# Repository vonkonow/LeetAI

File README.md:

# 🎹 Leet AI – A Tiny Synth Ensemble with AI-Powered Inspiration

Leet AI is a playful, pocket-sized synthesizer concept that explores what happens when many simple instruments work together—like a miniature electronic orchestra. Unlike traditional synths that try to do everything, Leet AI embraces a modular philosophy: multiple open-source, affordable units, each with a specific voice, combining to create something greater than the sum of their parts.

---

## 🌟 Why Leet AI?

Synthesizers can be intimidating. Menus, shift-buttons, and buried features can kill creative flow. Leet AI is an attempt to bring back the fun—tiny instruments you can pick up, jam with, and let the AI surprise you with new melodic ideas. Whether you're a tinkerer, a musician, or just curious about AI and music, this project is for you.

---

## ✨ Features

- 🎵 **AI-powered inspiration**  
  Generate unique melodies, drum patterns, and variations using a diffusion-based AI model.

- 🔧 **Hackable and open-source**  
  Built with CircuitPython on an ESP32-S2—plug it in, and you're editing the firmware like a USB stick.

- 🎛️ **Minimalist design with deep control**  
  Dual rotary encoders with tilt navigation, RGB-backlit keys, and a full-color display keep you focused and in control.

- 📶 **Wireless orchestration**  
  A low-latency protocol keeps multiple units in sync.

- 🔋 **Fully portable**  
  Runs on a rechargeable 1000mAh LiPo battery. Jam anywhere.

---

## 📦 Hardware Specs

- **Size:** 86 x 60 x 15 mm (smaller than a deck of cards!)
- **Keys:** 16 RGB-backlit mechanical keys
- **Microcontroller:** ESP32-S2 (CircuitPython firmware)
- **Display:** 1.8” 160x128 TFT color screen
- **Encoders:** Dual magnetic rotary encoders with tilt function
- **Audio:** High-quality 112dB SNR DAC
- **Connectivity:** MIDI over USB-C, ESP-Now wireless sync
- **Power:** 1000mAh LiPo battery with onboard charging

---

# ▶️ **Demo video** 

---

## 🧪 Build Difficulty 

**Medium.** You'll need SMD soldering skills, a 3D printer, and some patience and curiosity.

---

## 🛠️ Development History

Leet AI combines the best aspects of three earlier open hardware projects: [**leet**](https://vonkonow.com/leet-synthesizer/), [**leet modular**](https://vonkonow.com/leet-modular/), and [**chip champ**](https://vonkonow.com/chipchamp/). Prototypes have evolved through countless iterations—from hand-wired mock-ups to a 12-key prototype and finally to the 16-key design that bridges sequencer and keyboard layouts.

---

## 🚧 Limitations (For Now)

This is still a conceptual prototype. While it’s fully functional for the demo, many features are hardcoded. Here’s what’s next on the roadmap:

- 🎚️ Real-time editing and melody creation  
- 🎵 Higher-fidelity audio engine and custom graphic module
- 🎛️ Instrument selection and sound design (ADSR, filters, etc.)  
- 🧠 Smarter AI integration with automatic Wi-Fi server connection  
- 🎹 Stacked octave mode  
- 🔊 Optional speaker  
- 🎶 AMY synth library support?

---

## 🛒 BOM / Estimated Cost

**Total cost per unit:** ~$24

---

## 💡 Contributing

Got ideas? Want to help improve the synth engine, optimize graphics, or design new enclosures? All contributions—code, hardware, or creative—are welcome!

### ➕ How to Contribute

1. Fork the repo  
2. Try the demo firmware  
3. Submit issues or pull requests  
4. Join the discussion on hardware, AI models, or interface design

---

## 📁 Repository Structure

```
/
├── firmware/       → CircuitPython source code
├── hardware/       → KiCad files, schematics, and PCB layout
├── enclosure/      → 3D models (Rhino & STL)
├── ai-server/      → getMusic setup, scripts and generation tools
├── docs/           → Build guide, BOM, and reference images
└── README.md       → Project overview
```

---

## ❤️ Special Thanks

Huge thanks to the creators and maintainers of open-source tools that made this project possible.  
Special gratitude to [**Adafruit**](https://www.adafruit.com/) for developing [**CircuitPython**](https://circuitpython.org/board/lolin_s2_mini/), which made firmware development approachable, flexible, and fun—even for hardware newcomers.  
Thanks also to the team behind [**synthio**](https://docs.circuitpython.org/en/latest/shared-bindings/synthio/), whose powerful audio capabilities laid the groundwork for expressive, real-time sound generation on microcontrollers.  
And to Microsoft Research for [**getMusic**](https://github.com/microsoft/muzic), and to all the explorers at the intersection of music, AI, and creative technology—your curiosity and generosity continue to inspire.

---

## 🧠 Imagine What’s Next

Leet AI is still early, but the concept is alive. With your feedback, forks, and experiments, this can grow into a truly modular, generative instrument playground.

---

## 🔗 [Visit the project website  ](https://vonkonow.com/leetai/)
## 📂 [Explore the GitHub repository  ](https://github.com/vonkonow/leetai)
## 📸 [Share your builds and music!](https://vonkonow.com/community/)

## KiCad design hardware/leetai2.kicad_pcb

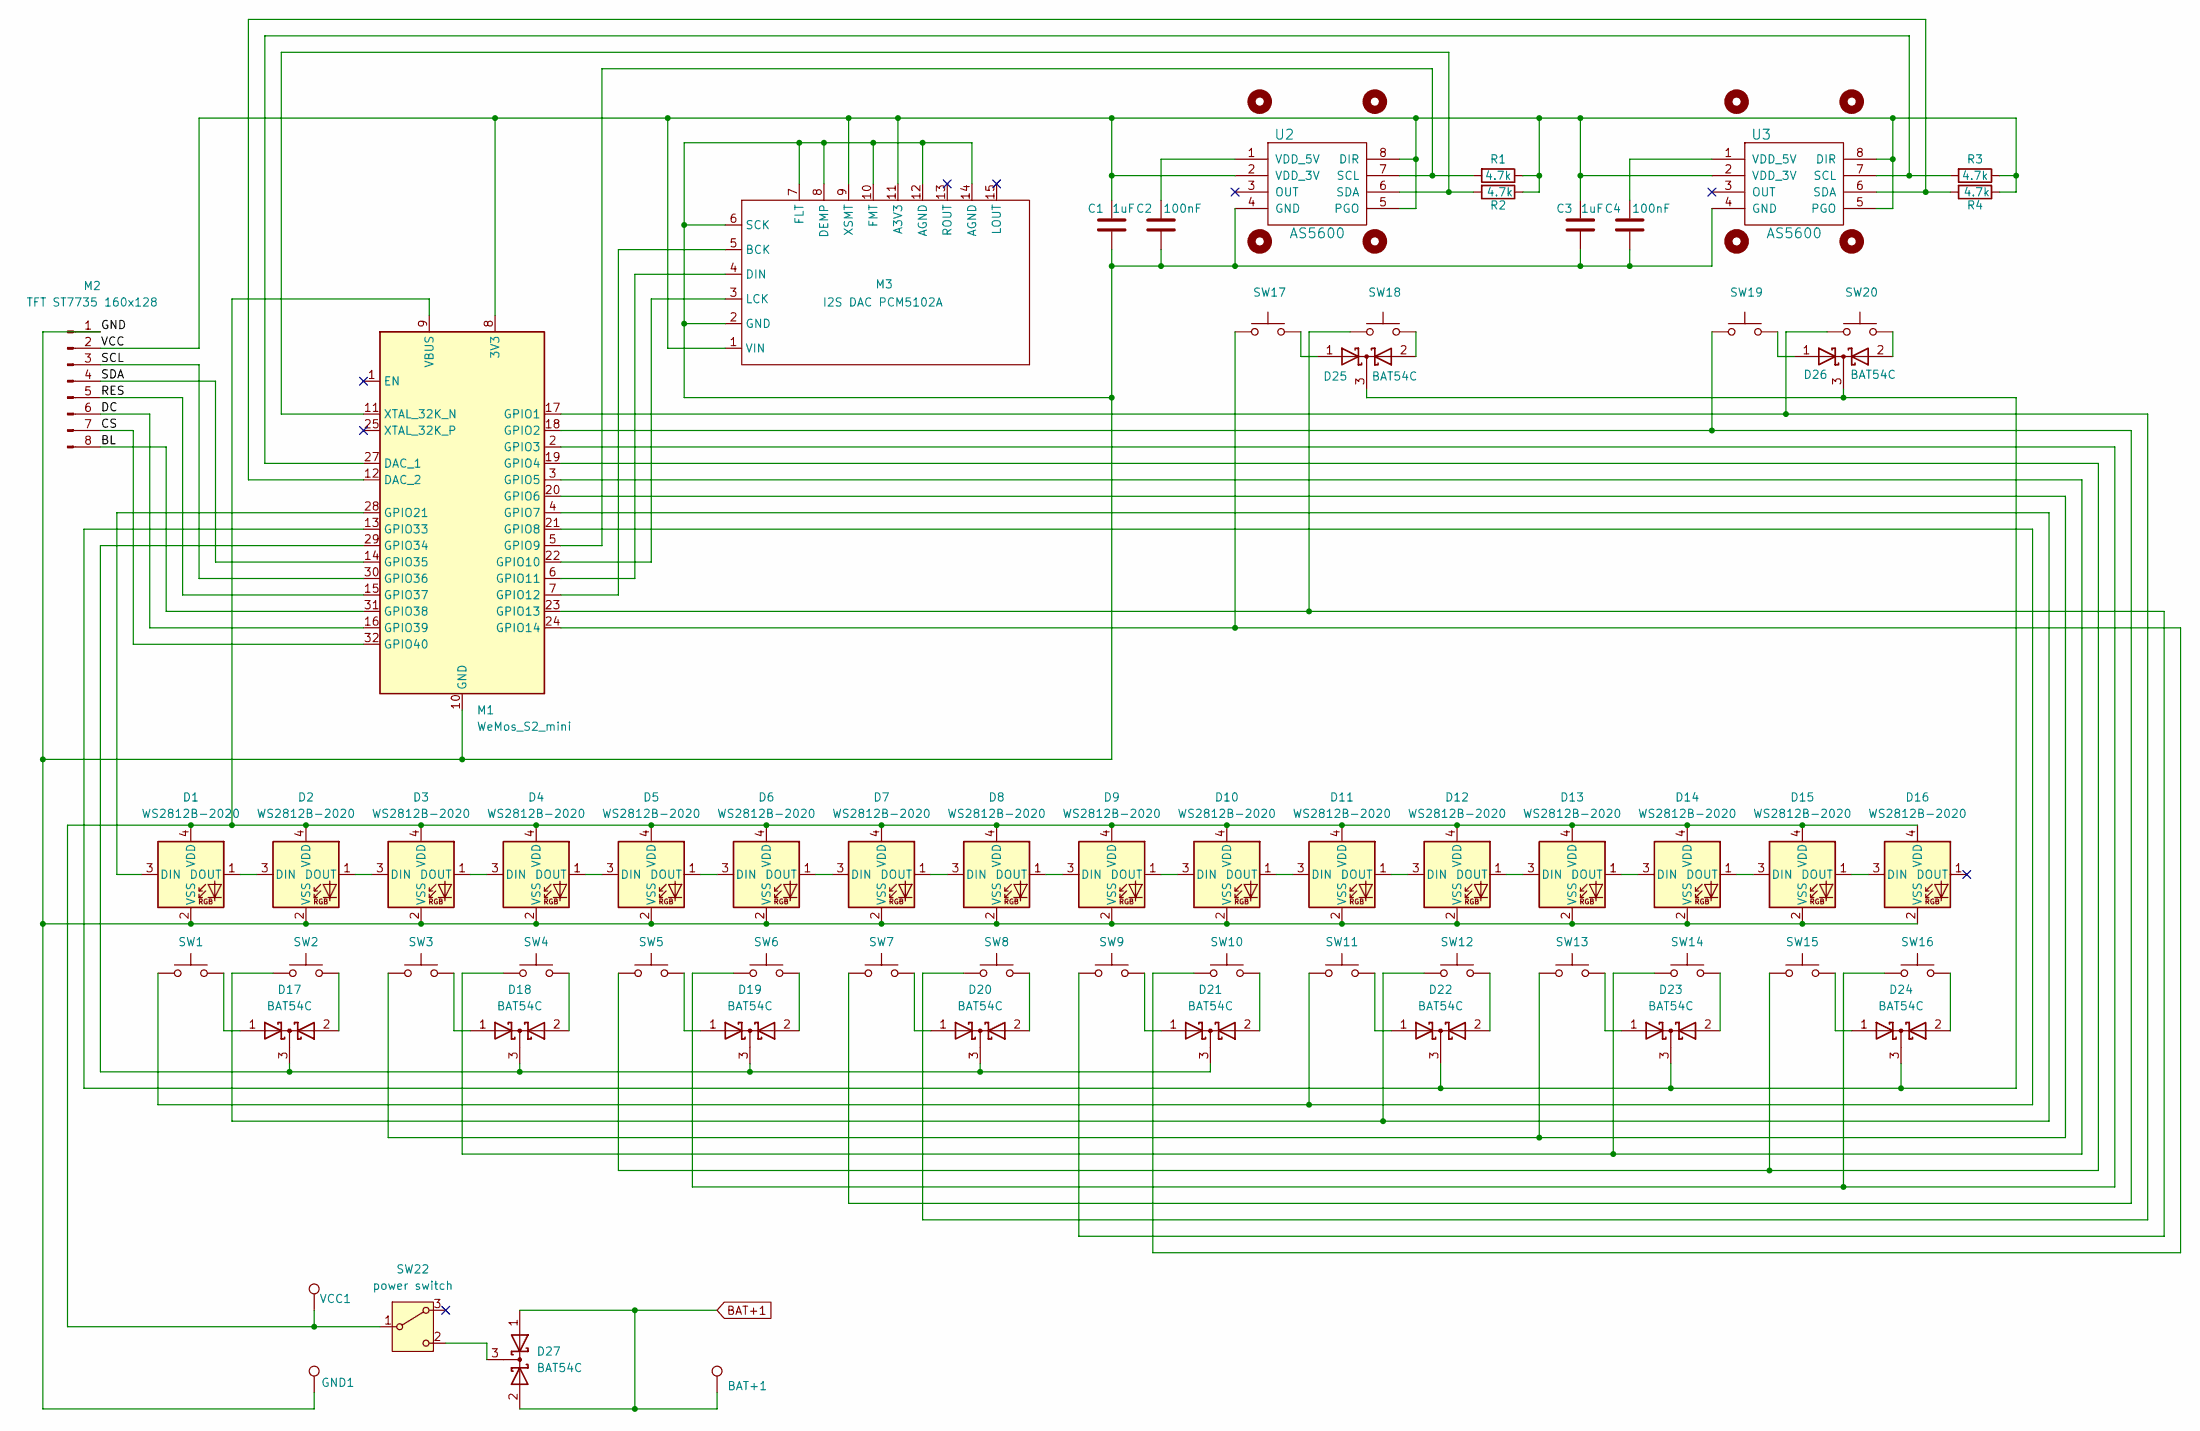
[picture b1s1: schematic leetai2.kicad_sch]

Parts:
BAT+1: Conn_01x01_Female; TestPoint_THTPad_2.5x2.5mm_Drill1.2mm
C1, C3: 1uF; C_0603_1608Metric_Pad1.08x0.95mm_HandSolder
C2, C4: 100nF; C_0603_1608Metric_Pad1.08x0.95mm_HandSolder
D1, D2, D3, D4, D5, D6, D7, D8, D9, D10, D11, D12, D13, D14, D15, D16: WS2812B-2020; LED_WS2812B-2020_PLCC4_2.0x2.0mm
D17, D18, D19, D20, D21, D22, D23, D24, D25, D26, D27: BAT54C; TSOT-23
GND1: Conn_01x01_Female; TestPoint_THTPad_2.5x2.5mm_Drill1.2mm
H1, H2, H3, H4, H5, H6, H7, H8: MountingHole; MountingHole_2mm
M1: WeMos_S2_mini; wemos_s2_mini
M2: TFT ST7735 160x128
M3: I2S DAC PCM5102A; I2S DAC 5102
R1, R2, R3, R4: 4.7k; R_0603_1608Metric_Pad0.98x0.95mm_HandSolder
SW1, SW2, SW3, SW4, SW5, SW6, SW7, SW8, SW9, SW10, SW11, SW12, SW13, SW14, SW15, SW16: SW_Omron_B3FS; switch_mouse_kailh_6x6
SW17, SW18, SW19, SW20: SW_Omron_B3FS; SW_Push_SPST_NO_Alps_SKRK
SW22: power switch; SW_Slide-03_Wuerth-WS-SLTV_10x2.5x6.4_P2.54mm
U2, U3: AS5600; SOIC-8_3.9x4.9mm_P1.27mm; Manufacturer Part Number AS5600-ASOM
VCC1: Conn_01x01_Female; TestPoint_THTPad_2.5x2.5mm_Drill1.2mm

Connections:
/BL: M1.31 (GPIO38), M2.8
/CS: M1.32 (GPIO40), M2.7
/DC: M1.16 (GPIO39), M2.6
/GND: C1.2, C2.1, C3.2, C4.1, D1.2 (VSS), D2.2 (VSS), D3.2 (VSS), D4.2 (VSS), D5.2 (VSS), D6.2 (VSS), D7.2 (VSS), D8.2 (VSS), D9.2 (VSS), D10.2 (VSS), D11.2 (VSS), D12.2 (VSS), D13.2 (VSS), D14.2 (VSS), D15.2 (VSS), D16.2 (VSS), GND1.1, M1.10 (GND), M1.26 (GND), M2.1, M3.2 (GND), M3.6 (SCK), M3.7 (FLT), M3.8 (DEMP), M3.10 (FMT), M3.12 (AGND), M3.14 (AGND), U2.4 (GND), U3.4 (GND)
/RES: M1.15 (GPIO37), M2.5
/SCL: M1.30 (GPIO36), M2.3
/SDA: M1.14 (GPIO35), M2.4
/VCC: C1.1, C3.1, M1.8 (3V3), M2.2, M3.1 (VIN), M3.9 (XSMT), M3.11 (A3V3), R1.1, R2.1, R3.1, R4.1, U2.2 (VDD_3V), U2.5 (PGO), U2.8 (DIR), U3.2 (VDD_3V), U3.5 (PGO), U3.8 (DIR)
BAT+1: BAT+1.1, D27.1 (A), D27.2 (A); also elsewhere on the board
unnamed: D1.3 (DIN), M1.28 (GPIO21)
unnamed: D1.1 (DOUT), D2.3 (DIN)
unnamed: D1.4 (VDD), D2.4 (VDD), D3.4 (VDD), D4.4 (VDD), D5.4 (VDD), D6.4 (VDD), D7.4 (VDD), D8.4 (VDD), D9.4 (VDD), D10.4 (VDD), D11.4 (VDD), D12.4 (VDD), D13.4 (VDD), D14.4 (VDD), D15.4 (VDD), D16.4 (VDD), M1.9 (VBUS), SW22.1 (B), VCC1.1
unnamed: D2.1 (DOUT), D3.3 (DIN)
unnamed: D3.1 (DOUT), D4.3 (DIN)
unnamed: D4.1 (DOUT), D5.3 (DIN)
unnamed: D5.1 (DOUT), D6.3 (DIN)
unnamed: D6.1 (DOUT), D7.3 (DIN)
unnamed: D7.1 (DOUT), D8.3 (DIN)
unnamed: D8.1 (DOUT), D9.3 (DIN)
unnamed: D9.1 (DOUT), D10.3 (DIN)
unnamed: D10.1 (DOUT), D11.3 (DIN)
unnamed: D11.1 (DOUT), D12.3 (DIN)
unnamed: D12.1 (DOUT), D13.3 (DIN)
unnamed: D13.1 (DOUT), D14.3 (DIN)
unnamed: D14.1 (DOUT), D15.3 (DIN)
unnamed: D15.1 (DOUT), D16.3 (DIN)
unnamed: D17.1 (A), SW1.2
unnamed: D17.2 (A), SW2.2
unnamed: D17.3 (K), D18.3 (K), D19.3 (K), D20.3 (K), D21.3 (K), M1.29 (GPIO34)
unnamed: D18.1 (A), SW3.2
unnamed: D18.2 (A), SW4.2
unnamed: D19.1 (A), SW5.2
unnamed: D19.2 (A), SW6.2
unnamed: D20.1 (A), SW7.2
unnamed: D20.2 (A), SW8.2
unnamed: D21.1 (A), SW9.2
unnamed: D21.2 (A), SW10.2
unnamed: D22.1 (A), SW11.2
unnamed: D22.2 (A), SW12.2
unnamed: D22.3 (K), D23.3 (K), D24.3 (K), D25.3 (K), D26.3 (K), M1.13 (GPIO33)
unnamed: D23.1 (A), SW13.2
unnamed: D23.2 (A), SW14.2
unnamed: D24.1 (A), SW15.2
unnamed: D24.2 (A), SW16.2
unnamed: D25.1 (A), SW17.2
unnamed: D25.2 (A), SW18.2
unnamed: D26.1 (A), SW19.2
unnamed: D26.2 (A), SW20.2
unnamed: D27.3 (K), SW22.2 (C)
unnamed: M1.27 (DAC_1), R3.2, U3.7 (SCL)
unnamed: M1.12 (DAC_2), R4.2, U3.6 (SDA)
unnamed: M1.17 (GPIO1), SW8.1, SW20.1
unnamed: M1.18 (GPIO2), SW7.1, SW19.1
unnamed: M1.2 (GPIO3), SW6.1, SW16.1
unnamed: M1.19 (GPIO4), SW5.1, SW15.1
unnamed: M1.3 (GPIO5), SW4.1, SW14.1
unnamed: M1.20 (GPIO6), SW3.1, SW13.1
unnamed: M1.4 (GPIO7), SW2.1, SW12.1
unnamed: M1.21 (GPIO8), SW1.1, SW11.1
unnamed: M1.5 (GPIO9), R1.2, U2.7 (SCL)
unnamed: M1.22 (GPIO10), M3.3 (LCK)
unnamed: M1.6 (GPIO11), M3.4 (DIN)
unnamed: M1.7 (GPIO12), M3.5 (BCK)
unnamed: M1.23 (GPIO13), SW9.1, SW18.1
unnamed: M1.24 (GPIO14), SW10.1, SW17.1
unnamed: M1.11 (XTAL_32K_N), R2.2, U2.6 (SDA)
unnamed: C2.2, U2.1 (VDD_5V)
unnamed: C4.2, U3.1 (VDD_5V)

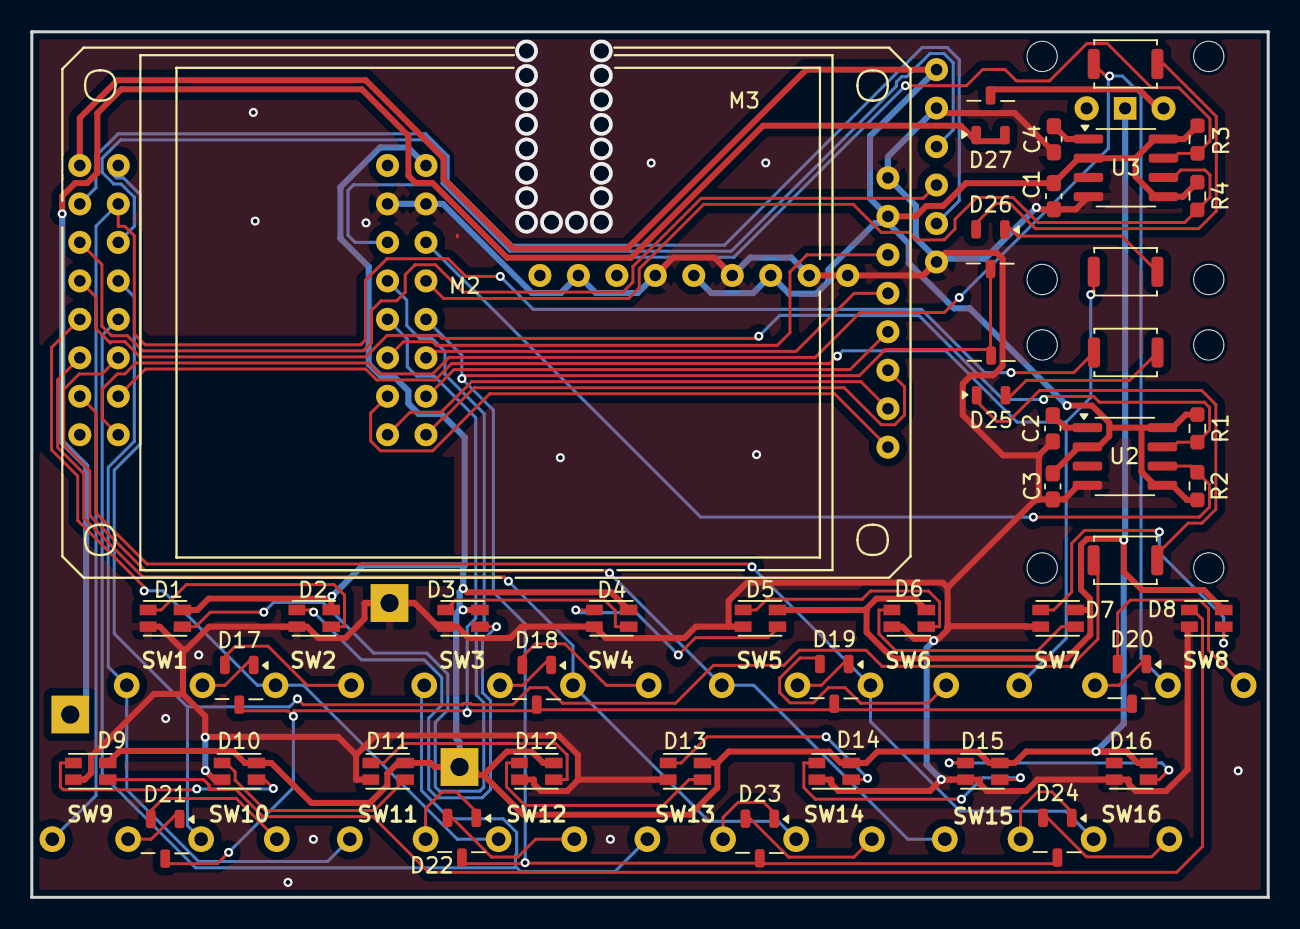
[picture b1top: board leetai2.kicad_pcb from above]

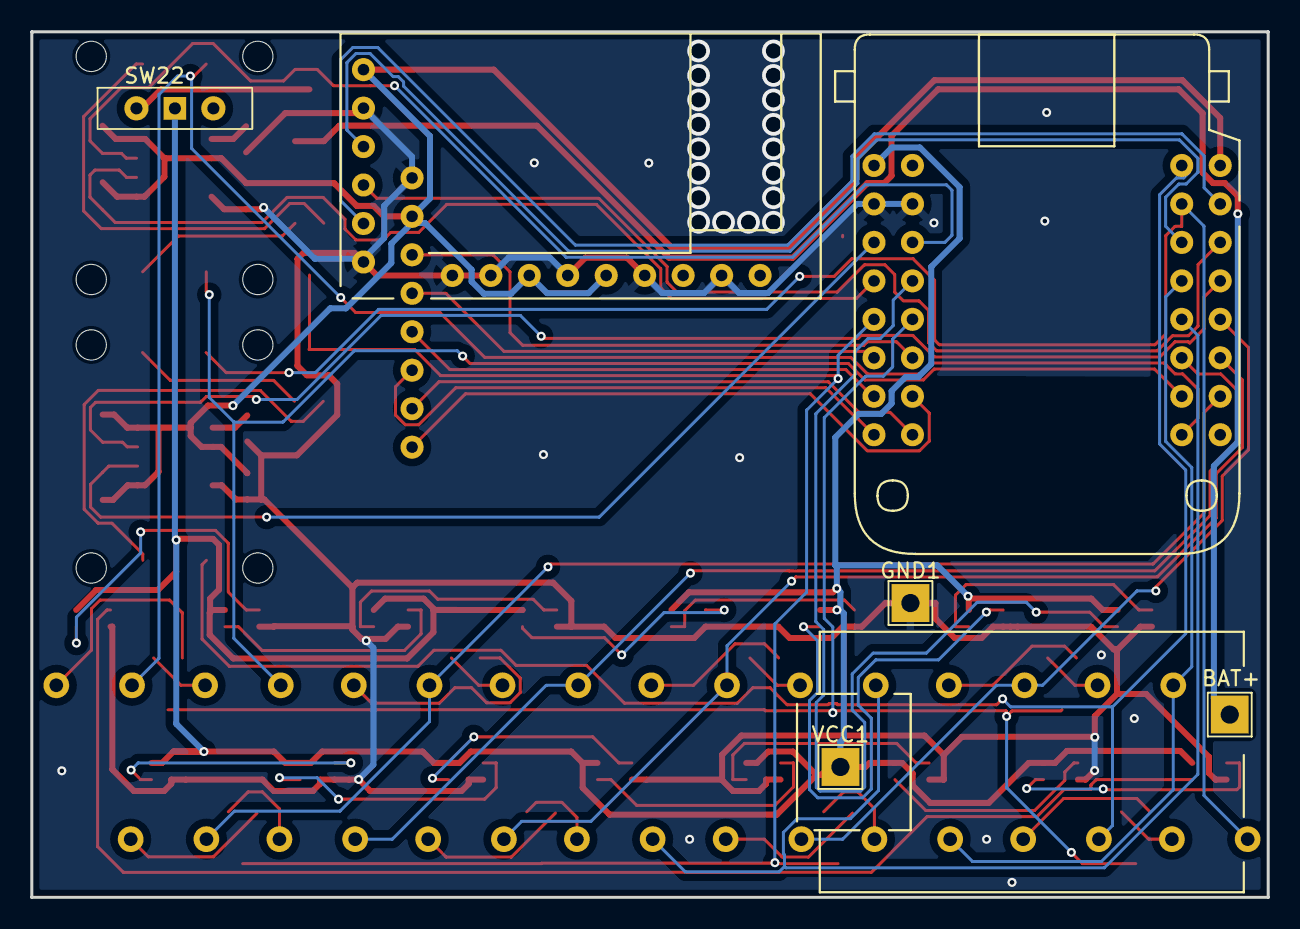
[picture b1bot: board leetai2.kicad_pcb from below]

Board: 2 copper layers, 81.6 x 57.2 mm, 72 parts (5 on the bottom side), 68 nets.

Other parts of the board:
BAT+: Conn_01x01_Female; TestPoint_THTPad_2.5x2.5mm_Drill1.2mm

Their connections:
BAT+1: BAT+.1; also elsewhere on the board

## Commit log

2025-05-04 project description
2025-05-04 updated repository description
2025-05-04 added folder structure
